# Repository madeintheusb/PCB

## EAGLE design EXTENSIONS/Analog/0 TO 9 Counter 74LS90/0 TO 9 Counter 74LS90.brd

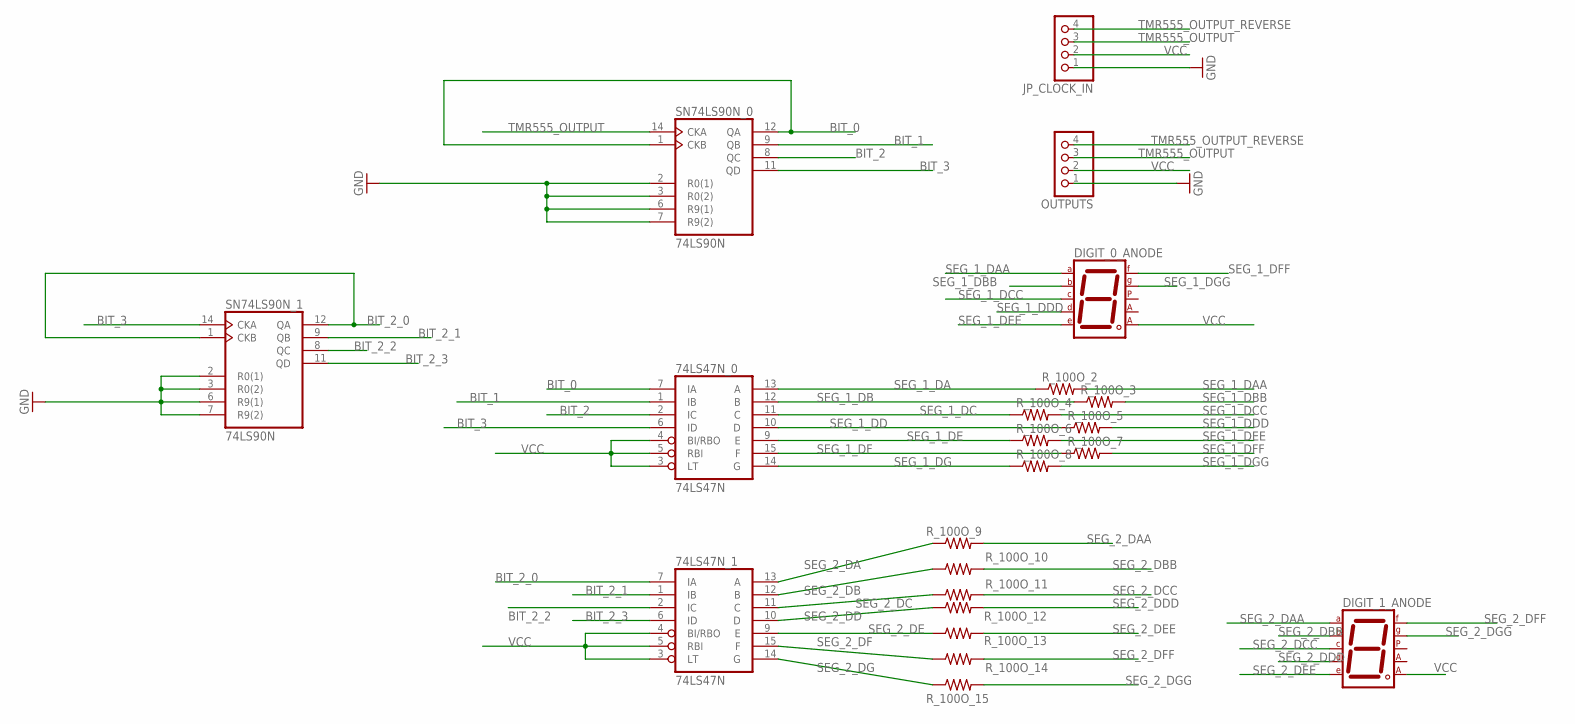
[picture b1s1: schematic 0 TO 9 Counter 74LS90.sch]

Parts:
74LS47N_0, 74LS47N_1: 74LS47N; DIL16
DIGIT_0_ANODE, DIGIT_1_ANODE: 7SEG-CA; 7SEG-13
JP_CLOCK_IN: PINHD-1X4; 1X04
OUTPUTS: PINHD-1X4; 1X04
R_100O_2, R_100O_3, R_100O_4, R_100O_5, R_100O_6, R_100O_7, R_100O_8, R_100O_9, R_100O_10, R_100O_11, R_100O_12, R_100O_13, R_100O_14, R_100O_15: R-US_R1206; R1206
SN74LS90N_0, SN74LS90N_1: 74LS90N; DIL14

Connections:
BIT_0: 74LS47N_0.7 (IA), SN74LS90N_0.1 (CKB), SN74LS90N_0.12 (QA)
BIT_1: 74LS47N_0.1 (IB), SN74LS90N_0.9 (QB)
BIT_2: 74LS47N_0.2 (IC), SN74LS90N_0.8 (QC)
BIT_2_0: 74LS47N_1.7 (IA), SN74LS90N_1.1 (CKB), SN74LS90N_1.12 (QA)
BIT_2_1: 74LS47N_1.1 (IB), SN74LS90N_1.9 (QB)
BIT_2_2: 74LS47N_1.2 (IC), SN74LS90N_1.8 (QC)
BIT_2_3: 74LS47N_1.6 (ID), SN74LS90N_1.11 (QD)
BIT_3: 74LS47N_0.6 (ID), SN74LS90N_0.11 (QD), SN74LS90N_1.14 (CKA)
GND: 74LS47N_0.8 (GND), 74LS47N_1.8 (GND), JP_CLOCK_IN.1, OUTPUTS.1, SN74LS90N_0.2 (R0(1)), SN74LS90N_0.3 (R0(2)), SN74LS90N_0.6 (R9(1)), SN74LS90N_0.7 (R9(2)), SN74LS90N_0.10 (GND), SN74LS90N_1.2 (R0(1)), SN74LS90N_1.3 (R0(2)), SN74LS90N_1.6 (R9(1)), SN74LS90N_1.7 (R9(2)), SN74LS90N_1.10 (GND)
SEG_1_DA: 74LS47N_0.13 (A), R_100O_2.1
SEG_1_DAA: DIGIT_0_ANODE.7 (A), R_100O_2.2
SEG_1_DB: 74LS47N_0.12 (B), R_100O_3.1
SEG_1_DBB: DIGIT_0_ANODE.6 (B), R_100O_3.2
SEG_1_DC: 74LS47N_0.11 (C), R_100O_4.1
SEG_1_DCC: DIGIT_0_ANODE.4 (C), R_100O_4.2
SEG_1_DD: 74LS47N_0.10 (D), R_100O_5.1
SEG_1_DDD: DIGIT_0_ANODE.2 (D), R_100O_5.2
SEG_1_DE: 74LS47N_0.9 (E), R_100O_6.1
SEG_1_DEE: DIGIT_0_ANODE.1 (E), R_100O_6.2
SEG_1_DF: 74LS47N_0.15 (F), R_100O_7.1
SEG_1_DFF: DIGIT_0_ANODE.9 (F), R_100O_7.2
SEG_1_DG: 74LS47N_0.14 (G), R_100O_8.1
SEG_1_DGG: DIGIT_0_ANODE.10 (G), R_100O_8.2
SEG_2_DA: 74LS47N_1.13 (A), R_100O_9.1
SEG_2_DAA: DIGIT_1_ANODE.7 (A), R_100O_9.2
SEG_2_DB: 74LS47N_1.12 (B), R_100O_10.1
SEG_2_DBB: DIGIT_1_ANODE.6 (B), R_100O_10.2
SEG_2_DC: 74LS47N_1.11 (C), R_100O_11.1
SEG_2_DCC: DIGIT_1_ANODE.4 (C), R_100O_11.2
SEG_2_DD: 74LS47N_1.10 (D), R_100O_12.1
SEG_2_DDD: DIGIT_1_ANODE.2 (D), R_100O_12.2
SEG_2_DE: 74LS47N_1.9 (E), R_100O_13.1
SEG_2_DEE: DIGIT_1_ANODE.1 (E), R_100O_13.2
SEG_2_DF: 74LS47N_1.15 (F), R_100O_14.1
SEG_2_DFF: DIGIT_1_ANODE.9 (F), R_100O_14.2
SEG_2_DG: 74LS47N_1.14 (G), R_100O_15.1
SEG_2_DGG: DIGIT_1_ANODE.10 (G), R_100O_15.2
TMR555_OUTPUT: JP_CLOCK_IN.3, OUTPUTS.3, SN74LS90N_0.14 (CKA)
TMR555_OUTPUT_REVERSE: JP_CLOCK_IN.4, OUTPUTS.4
VCC: 74LS47N_0.3 (LT), 74LS47N_0.4 (BI/RBO), 74LS47N_0.5 (RBI), 74LS47N_0.16 (VCC), 74LS47N_1.3 (LT), 74LS47N_1.4 (BI/RBO), 74LS47N_1.5 (RBI), 74LS47N_1.16 (VCC), DIGIT_0_ANODE.8 (CA2), DIGIT_1_ANODE.8 (CA2), JP_CLOCK_IN.2, OUTPUTS.2, SN74LS90N_0.5 (VCC), SN74LS90N_1.5 (VCC)

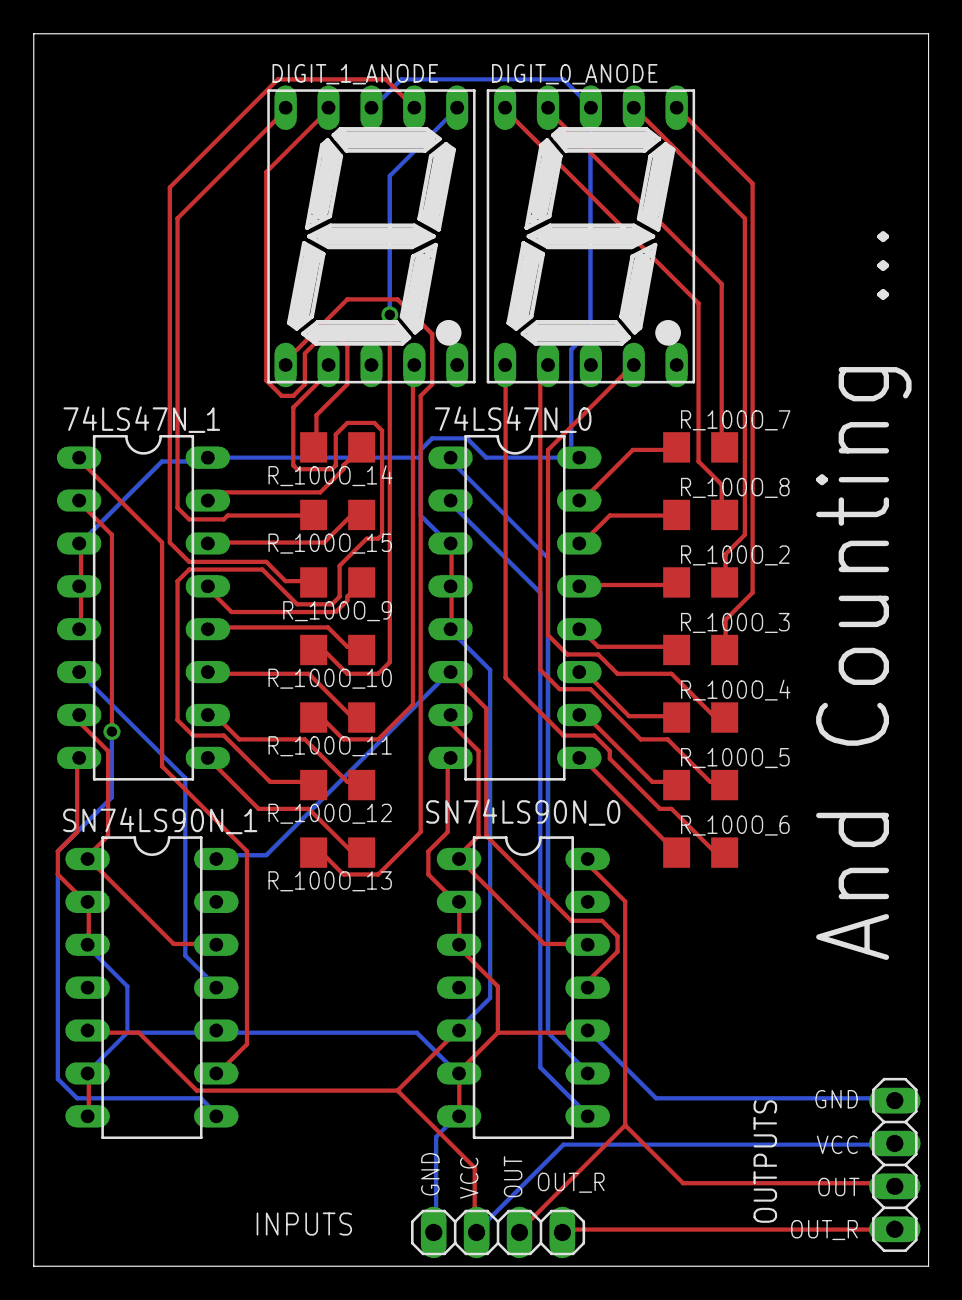
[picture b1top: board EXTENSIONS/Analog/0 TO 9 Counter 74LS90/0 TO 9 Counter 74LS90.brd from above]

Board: 2 copper layers, 53.0 x 73.0 mm, 22 parts (0 on the bottom side), 40 nets.

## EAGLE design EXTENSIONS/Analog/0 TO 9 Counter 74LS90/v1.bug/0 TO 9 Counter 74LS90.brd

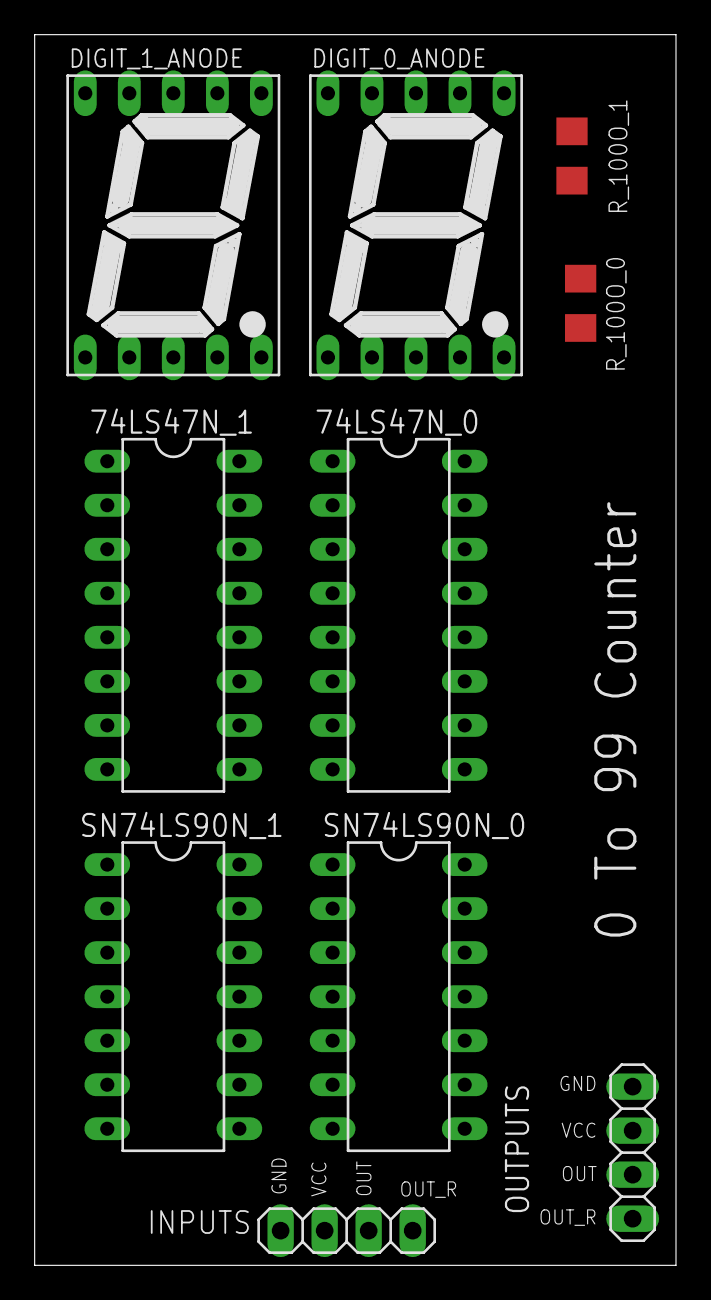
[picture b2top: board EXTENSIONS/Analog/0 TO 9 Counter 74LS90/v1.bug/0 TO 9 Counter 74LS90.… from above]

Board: 2 copper layers, 37.0 x 71.0 mm, 10 parts (0 on the bottom side), 27 nets, no tracks yet.

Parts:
74LS47N_0, 74LS47N_1: 74LS47N; DIL16
DIGIT_0_ANODE, DIGIT_1_ANODE: 7SEG-13
JP_CLOCK_IN: 1X04
OUTPUTS: 1X04
R_100O_0, R_100O_1: R1206
SN74LS90N_0, SN74LS90N_1: 74LS90N; DIL14

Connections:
BIT_0: 74LS47N_0.7, SN74LS90N_0.1, SN74LS90N_0.12
BIT_1: 74LS47N_0.1, SN74LS90N_0.9
BIT_2: 74LS47N_0.2, SN74LS90N_0.8
BIT_2_0: 74LS47N_1.7, SN74LS90N_1.1, SN74LS90N_1.12
BIT_2_1: 74LS47N_1.1, SN74LS90N_1.9
BIT_2_2: 74LS47N_1.2, SN74LS90N_1.8
BIT_2_3: 74LS47N_1.6, SN74LS90N_1.11
BIT_3: 74LS47N_0.6, SN74LS90N_0.11
GND: 74LS47N_0.8, 74LS47N_1.8, JP_CLOCK_IN.1, OUTPUTS.1, SN74LS90N_0.2, SN74LS90N_0.3, SN74LS90N_0.6, SN74LS90N_0.7, SN74LS90N_0.10, SN74LS90N_1.2, SN74LS90N_1.3, SN74LS90N_1.6, SN74LS90N_1.7, SN74LS90N_1.10
unnamed: DIGIT_0_ANODE.8, R_100O_0.1
unnamed: DIGIT_1_ANODE.8, R_100O_1.1
SEG_1_DA: 74LS47N_0.13, DIGIT_0_ANODE.7
SEG_1_DB: 74LS47N_0.12, DIGIT_0_ANODE.6
SEG_1_DC: 74LS47N_0.11, DIGIT_0_ANODE.4
SEG_1_DD: 74LS47N_0.10, DIGIT_0_ANODE.2
SEG_1_DE: 74LS47N_0.9, DIGIT_0_ANODE.1
SEG_1_DF: 74LS47N_0.15, DIGIT_0_ANODE.9
SEG_2_DA: 74LS47N_1.13, DIGIT_1_ANODE.7
SEG_2_DB: 74LS47N_1.12, DIGIT_1_ANODE.6
SEG_2_DC: 74LS47N_1.11, DIGIT_1_ANODE.4
SEG_2_DD: 74LS47N_1.10, DIGIT_1_ANODE.2
SEG_2_DE: 74LS47N_1.9, DIGIT_1_ANODE.1
SEG_2_DF: 74LS47N_1.15, DIGIT_1_ANODE.9
SEG_2_DG: 74LS47N_1.14, DIGIT_1_ANODE.10
TMR555_OUTPUT: JP_CLOCK_IN.3, OUTPUTS.3, SN74LS90N_0.14
TMR555_OUTPUT_REVERSE: JP_CLOCK_IN.4, OUTPUTS.4
VCC: 74LS47N_0.3, 74LS47N_0.4, 74LS47N_0.5, 74LS47N_0.16, 74LS47N_1.3, 74LS47N_1.4, 74LS47N_1.5, 74LS47N_1.16, JP_CLOCK_IN.2, OUTPUTS.2, R_100O_0.2, R_100O_1.2, SN74LS90N_0.5, SN74LS90N_1.5

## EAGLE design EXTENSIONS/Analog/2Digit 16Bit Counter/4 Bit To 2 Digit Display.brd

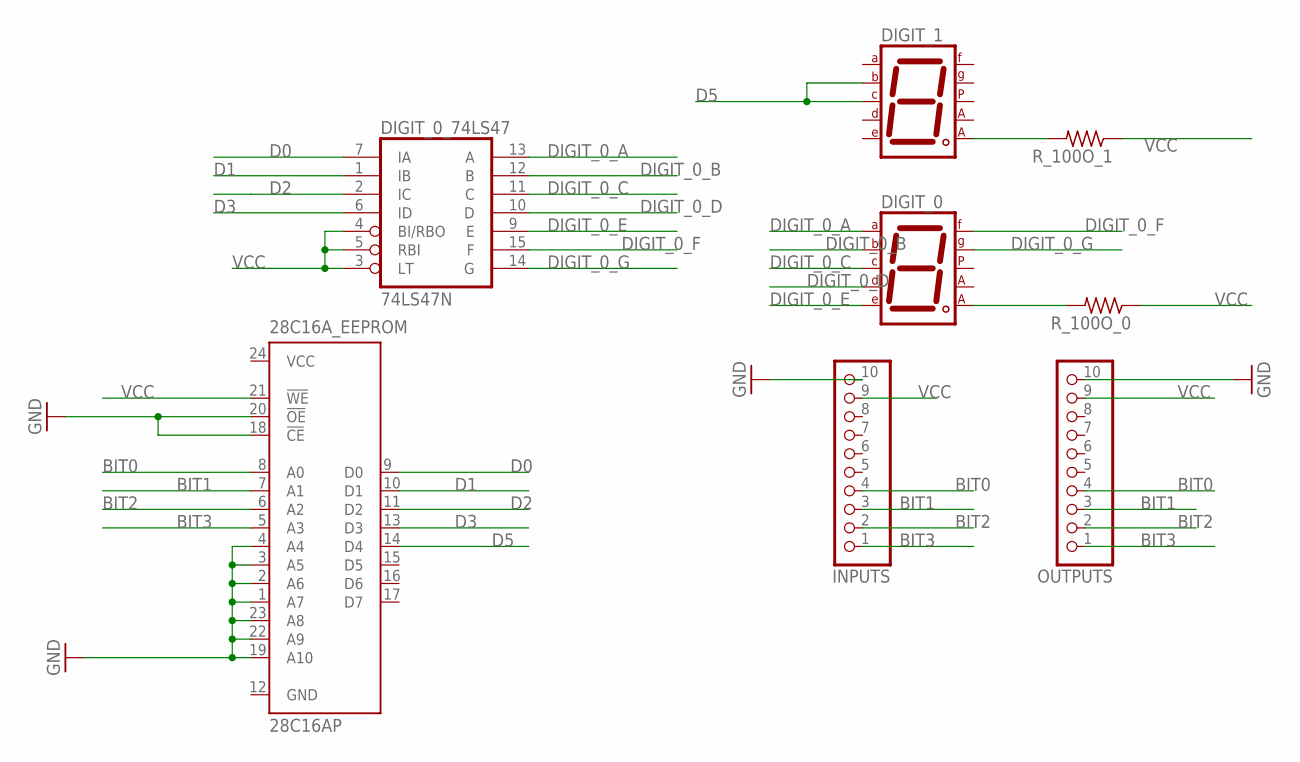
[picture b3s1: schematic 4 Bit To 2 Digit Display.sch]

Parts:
28C16A_EEPROM: 28C16AP; DIL24-6
DIGIT_0, DIGIT_1: 7SEG-CA; 7SEG-13
DIGIT_0_74LS47: 74LS47N; DIL16
INPUTS: PINHD-1X10; 1X10-BIG
OUTPUTS: PINHD-1X10; 1X10-BIG
R_100O_0, R_100O_1: R-US_R1206; R1206

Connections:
BIT0: 28C16A_EEPROM.8 (A0), INPUTS.4, OUTPUTS.4
BIT1: 28C16A_EEPROM.7 (A1), INPUTS.3, OUTPUTS.3
BIT2: 28C16A_EEPROM.6 (A2), INPUTS.2, OUTPUTS.2
BIT3: 28C16A_EEPROM.5 (A3), INPUTS.1, OUTPUTS.1
D0: 28C16A_EEPROM.9 (D0), DIGIT_0_74LS47.7 (IA)
D1: 28C16A_EEPROM.10 (D1), DIGIT_0_74LS47.1 (IB)
D2: 28C16A_EEPROM.11 (D2), DIGIT_0_74LS47.2 (IC)
D3: 28C16A_EEPROM.13 (D3), DIGIT_0_74LS47.6 (ID)
D5: 28C16A_EEPROM.14 (D4), DIGIT_1.4 (C), DIGIT_1.6 (B)
DIGIT_0_A: DIGIT_0.7 (A), DIGIT_0_74LS47.13 (A)
DIGIT_0_B: DIGIT_0.6 (B), DIGIT_0_74LS47.12 (B)
DIGIT_0_C: DIGIT_0.4 (C), DIGIT_0_74LS47.11 (C)
DIGIT_0_D: DIGIT_0.2 (D), DIGIT_0_74LS47.10 (D)
DIGIT_0_E: DIGIT_0.1 (E), DIGIT_0_74LS47.9 (E)
DIGIT_0_F: DIGIT_0.9 (F), DIGIT_0_74LS47.15 (F)
DIGIT_0_G: DIGIT_0.10 (G), DIGIT_0_74LS47.14 (G)
GND: 28C16A_EEPROM.1 (A7), 28C16A_EEPROM.2 (A6), 28C16A_EEPROM.3 (A5), 28C16A_EEPROM.4 (A4), 28C16A_EEPROM.12 (GND), 28C16A_EEPROM.18 (!CE), 28C16A_EEPROM.19 (A10), 28C16A_EEPROM.20 (!OE), 28C16A_EEPROM.22 (A9), 28C16A_EEPROM.23 (A8), DIGIT_0_74LS47.8 (GND), INPUTS.10, OUTPUTS.10
unnamed: DIGIT_0.8 (CA2), R_100O_0.2
unnamed: DIGIT_1.8 (CA2), R_100O_1.2
VCC: 28C16A_EEPROM.21 (!WE), 28C16A_EEPROM.24 (VCC), DIGIT_0_74LS47.3 (LT), DIGIT_0_74LS47.4 (BI/RBO), DIGIT_0_74LS47.5 (RBI), DIGIT_0_74LS47.16 (VCC), INPUTS.9, OUTPUTS.9, R_100O_0.1, R_100O_1.1

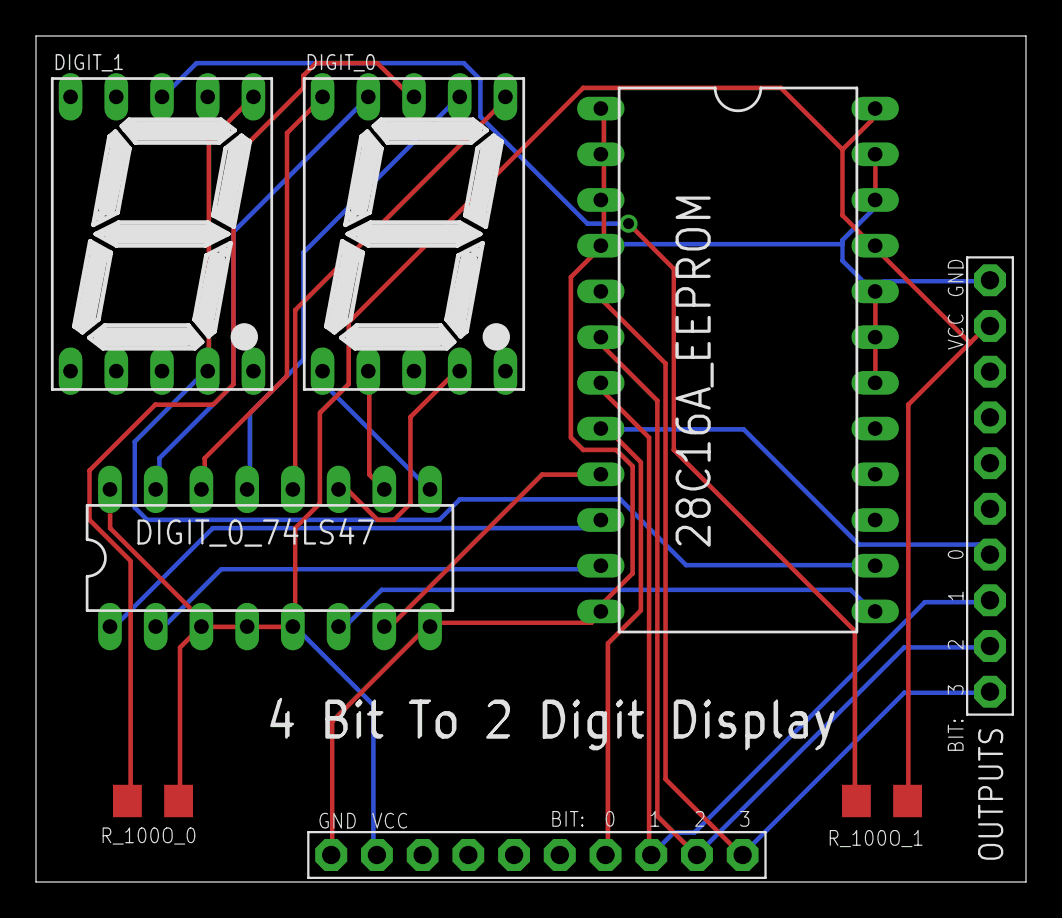
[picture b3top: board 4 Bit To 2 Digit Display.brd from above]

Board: 2 copper layers, 55.0 x 47.0 mm, 8 parts (0 on the bottom side), 20 nets.

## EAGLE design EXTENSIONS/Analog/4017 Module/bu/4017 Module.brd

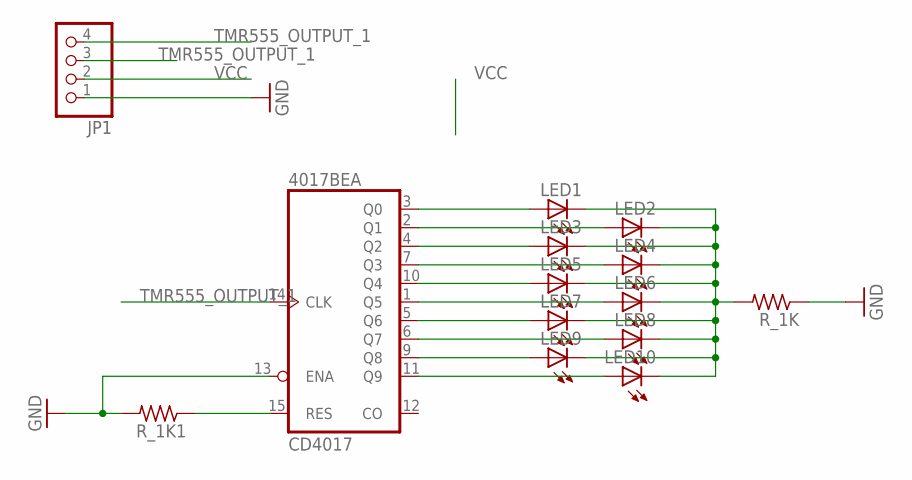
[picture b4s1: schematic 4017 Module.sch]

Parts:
4017BE: CD4017; DIL16
JP1: PINHD-1X4; 1X04
LED1, LED2, LED3, LED4, LED5, LED6, LED7, LED8, LED9, LED10: LEDSMT1206; 1206
R_1K, R_1K1: R-US_R1206; R1206

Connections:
GND: 4017BE.8 (GND), 4017BE.13 (ENA), JP1.1, R_1K.1, R_1K1.2
unnamed: 4017BE.3 (Q0), LED1.A
unnamed: 4017BE.2 (Q1), LED2.A
unnamed: 4017BE.4 (Q2), LED3.A
unnamed: 4017BE.7 (Q3), LED4.A
unnamed: 4017BE.10 (Q4), LED5.A
unnamed: 4017BE.1 (Q5), LED6.A
unnamed: 4017BE.5 (Q6), LED7.A
unnamed: 4017BE.6 (Q7), LED8.A
unnamed: 4017BE.9 (Q8), LED9.A
unnamed: 4017BE.11 (Q9), LED10.A
unnamed: LED1.C, LED2.C, LED3.C, LED4.C, LED5.C, LED6.C, LED7.C, LED8.C, LED9.C, LED10.C, R_1K.2
unnamed: 4017BE.15 (RES), R_1K1.1
TMR555_OUTPUT_1: 4017BE.14 (CLK), JP1.3, JP1.4
VCC: 4017BE.16 (VCC), JP1.2

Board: 2 copper layers, 14 parts (0 on the bottom side), 15 nets, no tracks yet.

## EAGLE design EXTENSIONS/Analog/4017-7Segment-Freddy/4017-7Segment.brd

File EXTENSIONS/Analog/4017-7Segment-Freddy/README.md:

# Freddy's 7-Segment Display Animation

How to create an animation using a [CD4017BE](http://www.ti.com/lit/ds/symlink/cd4017b.pdf) a decade counter and a lot of diodes.

* [Video](https://www.youtube.com/watch?v=Pmq1hEMuzKk)

* [Photos](https://www.flickr.com/photos/138302041@N06/albums/72157710833673621)

![schema(./4017-7Segment.schema.png)

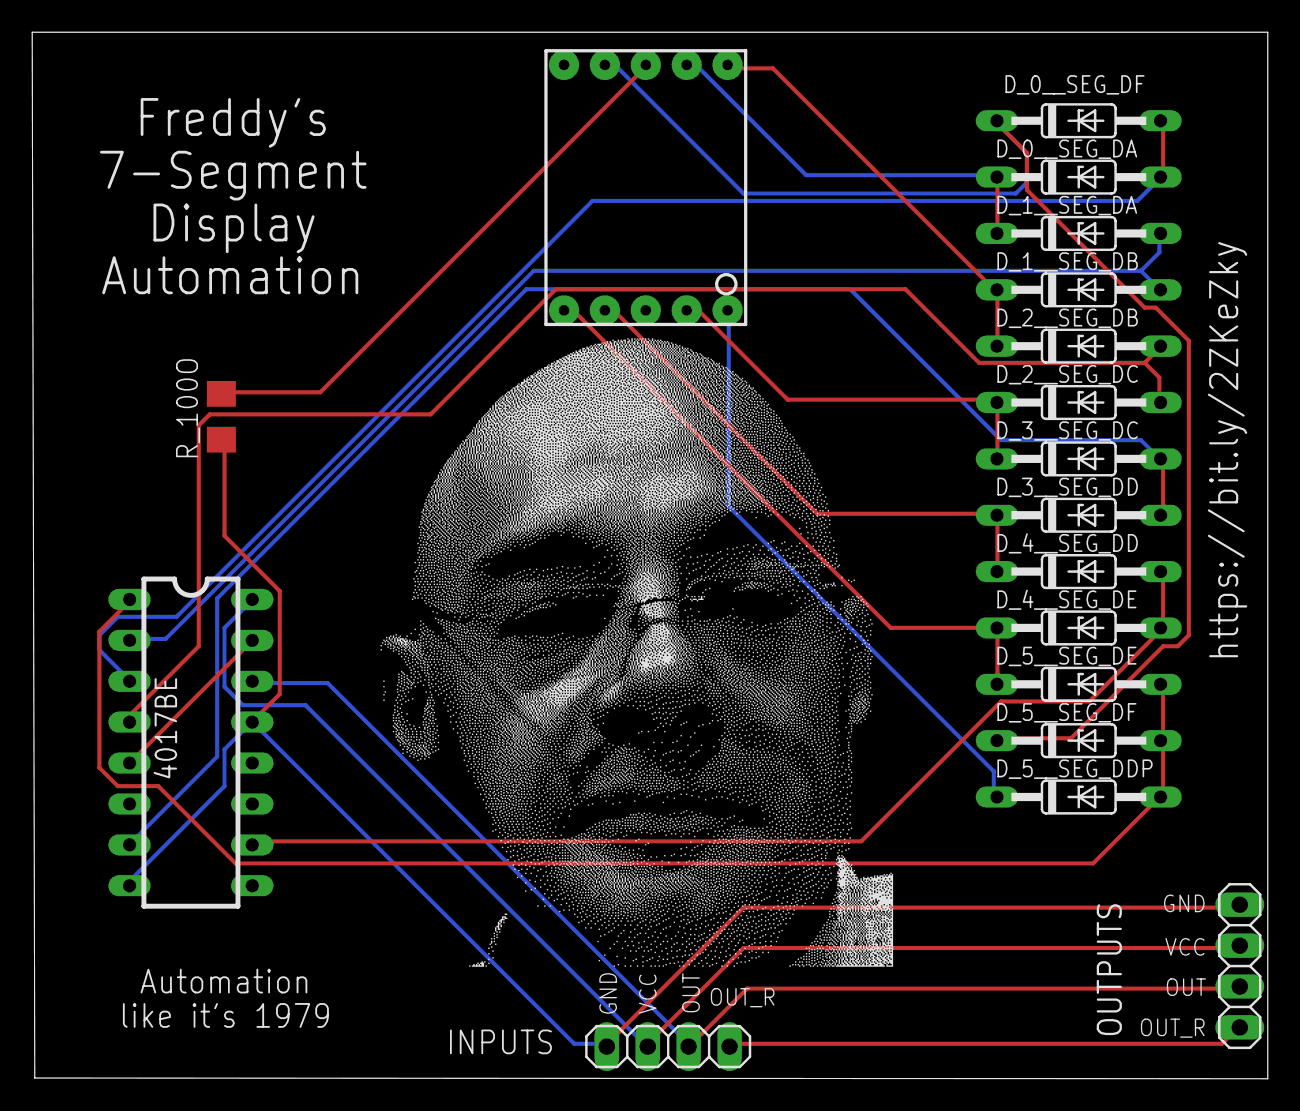
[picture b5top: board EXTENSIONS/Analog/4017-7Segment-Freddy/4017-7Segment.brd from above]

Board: 2 copper layers, 76.7 x 65.0 mm, 18 parts (0 on the bottom side), 19 nets.

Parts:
4017BE: CD4017; DIL16
D_0__SEG_DA, D_0__SEG_DF, D_1__SEG_DA, D_1__SEG_DB, D_2__SEG_DB, D_2__SEG_DC, D_3__SEG_DC, D_3__SEG_DD, D_4__SEG_DD, D_4__SEG_DE, D_5__SEG_DDP, D_5__SEG_DE, D_5__SEG_DF: 1N821; DO35Z10
JP_CLOCK_IN: 1X04
OUTPUTS: 1X04
R_100O: R1206
U$1: 7-SEGMENT-DISPLAYPTH; 7-SEGMENT-DISPLAY

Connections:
GND: 4017BE.8, 4017BE.13, JP_CLOCK_IN.1, OUTPUTS.1, R_100O.1
unnamed: R_100O.2, U$1.8
P_0: 4017BE.3, D_0__SEG_DA.A, D_0__SEG_DF.A
P_1: 4017BE.2, D_1__SEG_DA.A, D_1__SEG_DB.A
P_2: 4017BE.4, D_2__SEG_DB.A, D_2__SEG_DC.A
P_3: 4017BE.7, D_3__SEG_DC.A, D_3__SEG_DD.A
P_4: 4017BE.10, D_4__SEG_DD.A, D_4__SEG_DE.A
P_5: 4017BE.1, D_5__SEG_DDP.A, D_5__SEG_DE.A, D_5__SEG_DF.A
RESET: 4017BE.5, 4017BE.15
SEG_DA: D_0__SEG_DA.C, D_1__SEG_DA.C, U$1.7
SEG_DB: D_1__SEG_DB.C, D_2__SEG_DB.C, U$1.6
SEG_DC: D_2__SEG_DC.C, D_3__SEG_DC.C, U$1.4
SEG_DD: D_3__SEG_DD.C, D_4__SEG_DD.C, U$1.2
SEG_DDP: D_5__SEG_DDP.C, U$1.5
SEG_DE: D_4__SEG_DE.C, D_5__SEG_DE.C, U$1.1
SEG_DF: D_0__SEG_DF.C, D_5__SEG_DF.C, U$1.9
TMR555_OUTPUT: 4017BE.14, JP_CLOCK_IN.3, OUTPUTS.3
TMR555_OUTPUT_REVERSE: JP_CLOCK_IN.4, OUTPUTS.4
VCC: 4017BE.16, JP_CLOCK_IN.2, OUTPUTS.2

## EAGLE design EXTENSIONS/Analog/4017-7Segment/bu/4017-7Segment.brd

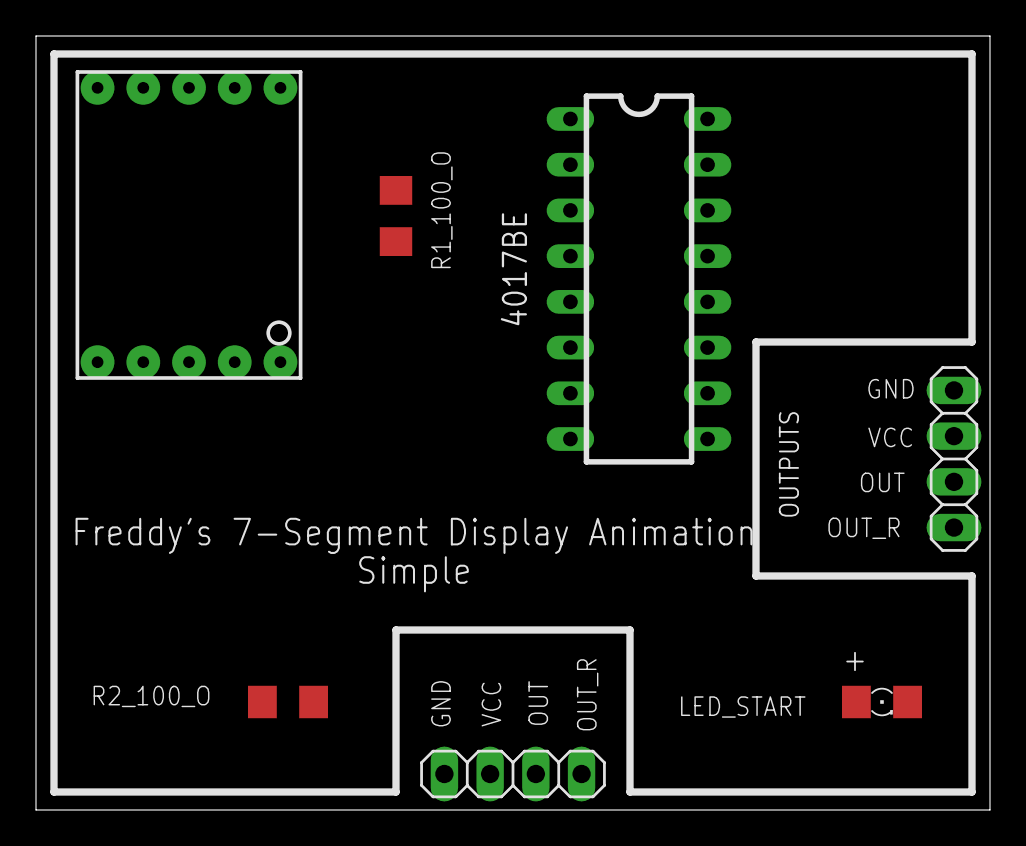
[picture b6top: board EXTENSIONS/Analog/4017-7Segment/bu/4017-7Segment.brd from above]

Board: 2 copper layers, 53.0 x 43.0 mm, 7 parts (0 on the bottom side), 14 nets, no tracks yet.

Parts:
4017BE: CD4017; DIL16
JP_CLOCK_IN: 1X04
LED_START: 1206
OUTPUTS: 1X04
R1_100_O, R2_100_O: R1206
U$1: 7-SEGMENT-DISPLAYPTH; 7-SEGMENT-DISPLAY

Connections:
GND: 4017BE.8, 4017BE.13, JP_CLOCK_IN.1, OUTPUTS.1, R1_100_O.1, R2_100_O.1
unnamed: LED_START.C, R2_100_O.2
unnamed: R1_100_O.2, U$1.8
RESET: 4017BE.6, 4017BE.15
SEG_A: 4017BE.3, LED_START.A, U$1.7
SEG_B: 4017BE.2, U$1.6
SEG_C: 4017BE.4, U$1.4
SEG_D: 4017BE.7, U$1.2
SEG_E: 4017BE.10, U$1.1
SEG_F: 4017BE.1, U$1.9
SEG_G: 4017BE.5, U$1.10
TMR555_OUTPUT: 4017BE.14, JP_CLOCK_IN.3, OUTPUTS.3
TMR555_OUTPUT_REVERSE: JP_CLOCK_IN.4, OUTPUTS.4
VCC: 4017BE.16, JP_CLOCK_IN.2, OUTPUTS.2

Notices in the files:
parts and their libraries:
SparkFun-DigitalIC: Licensing: Creative Commons ShareAlike 4.0 International - https://creativecommons.org/licenses/by-sa/4.0
